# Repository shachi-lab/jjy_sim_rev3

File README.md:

# 📡 JJY Simulator Rev.3 for ESP32-C3 / ESP8684

Build your own JJY time-signal simulator with an ESP32-C3 or ESP8684!  
This compact simulator reproduces the 40 kHz / 60 kHz JJY radio time signal using PWM output,  
based on accurate time obtained from NTP.  
Rev.3 is developed with ESP-IDF.  

Latest version: **R3-1.0.6**

👉 [README 日本語版はこちら](README_ja.md)

---

## 🪛 Features

* Supports both **ESP32-C3** and **ESP8684**
* Full-featured implementation based on **ESP-IDF**
* **Easy AP mode** for Wi-Fi setup with a single button
* **OLED display** for checking the current time and sync status
* Automatic time synchronization via **NTP**
* Switchable **JJY 40 kHz (eastern Japan) / 60 kHz (western Japan)**
* Output **band optimization** can be selected with an on-board switch
* Signal is radiated from a built-in **simple antenna** on the board
* **H-bridge output stage** for higher output power (may transmit farther than expected)
* Configuration page accessible from a **web browser**
* Supports **time zones** and **DST (Daylight Saving Time)**
* **Hourly Mode** for periodic JJY signal output
* **Night Mode** for reducing OLED display brightness at night
* **Offset Time** adjustment for fine-tuning the transmitted time
* Displays a **clock screen** during operation

<br/>

---

## 🛠 Build and Flash (ESP-IDF / CLI)

JJY-SIM R3 is built and flashed using ESP-IDF.  
R2 was Arduino-based,  
but R3 has moved to ESP-IDF for better timing accuracy and a cleaner overall architecture.

> ### ⚠️ Note
> * This project cannot be built in the Arduino environment
> * This is an ESP-IDF-only project

### ■ Environment

* ESP-IDF v5.x
* Python (with a working `idf.py` environment)

For ESP-IDF setup, please refer to the official documentation.

### ■ Build

Move to the project directory and run:

```bash
idf.py build
```

### ■ Flash

```bash
idf.py flash
```

If you need to specify the serial port:

```bash
idf.py -p COMx flash
```

### ■ Serial Monitor

```bash
idf.py monitor
```

### ■ Full Command

```bash
idf.py -p COMx flash monitor
```

This single command lets you flash the firmware and open the log output at the same time.

### ■ Target Selection

Set the target once during initial setup.
The required target depends on which module you are using.

* When using **ESP32-C3**:

```bash
idf.py set-target esp32c3
```

* When using **ESP8684**:
  Since the ESP8684 is based on **ESP32-C2**,
  select `esp32c2` as the chip target.

```bash
idf.py set-target esp32c2
```

---

## 🛠 Build and Flash (VSCode / GUI)

You can also develop this project using **VSCode + the ESP-IDF Extension**.

### ■ Recommended Extension

* ESP-IDF Extension (Espressif)

By installing the extension in VSCode, you can perform the following from the GUI:

* Build
* Flash
* Serial monitor

### ■ Setup

Set up your environment according to the ESP-IDF Extension instructions.

Once the extension is installed, you can run actions such as:

* `Build`
* `Flash`
* `Monitor`

with a single click.

### ■ Workspace

When opening the project in VSCode,
open **`jjy-sim-r3.code-workspace`** in the source-code folder
to work with the ESP-IDF Extension settings already included.

---

## ⚙️ Usage

### ■ Wi-Fi Setup

* After power-on or reset, press the **CONFIG** switch within 5 seconds  
  On first boot, the device enters Wi-Fi setup mode automatically
* An AP named `JJY-SIM-R3-XXXXXXXX` will start
* Connect from a smartphone or PC → a captive portal will appear
* Select the SSID and enter the password
* You can also configure the band, local time, and DST (Daylight Saving Time) as needed
* Click **[Save and Reboot]** to save the settings and restart the device

### ■ Operation Check

* After power-on or reset, the logo is shown. If left untouched for 5 seconds, the device will try to connect to the configured Wi-Fi AP
* Once connected, it obtains the current time from an NTP server
* The current time is shown on the OLED, and JJY signal output starts from second 0 using PWM
* Just press the **receive button** on your radio-controlled clock and place it nearby

### ■ Controls During Operation

While the clock screen is displayed, the following operations are available:

* Press the **[CONFIG]** button for about 1 second to show the information screen  
  Press **[CONFIG]** again to return to the clock screen
* Press and hold the **[CONFIG]** button for 5 seconds or longer to stop JJY transmission output  
  Press and hold **[CONFIG]** again for 5 seconds or longer to resume JJY transmission output

---

## 🔌 Pin Assignment (Main Signals)

| Function       | GPIO | Notes                                                        |
| -------------- | ---- | ------------------------------------------------------------ |
| JJY PWM output | 10,4 | Modulated output signals, inverted A/B pair for the H-bridge |
| CONFIG switch  | 9    | Used for Wi-Fi setup (**shared with BOOT pin**)              |
| ACT LED        | 5    | Activity LED                                                 |
| IND LED        | 0    | Status indicator LED (can be shared)                         |
| OLED Reset     | 2    | OLED module reset                                            |
| OLED SDA       | 7    | OLED I2C data                                                |
| OLED SCL       | 6    | OLED I2C clock                                               |

---

## 🧾 File Structure

### 💻 Firmware

* The firmware source code is located in the **`firmware/idf`** folder.
* This firmware uses a rebuilt library, ported as an IDF component, based on the Arduino OLED driver library used in R2.  
This component is publicly available on GitHub.  
👉 [SSD1306 OLED display driver](https://github.com/Shachi-lab/oled_display)
* `storage_key.h` contains placeholder values and can be used as-is.  
  For better security, you may want to replace them with your own values before building.

### 🧰 Hardware

* The hardware design files are located in the **`hardware`** folder.
* The schematic and PCB design data are in **`hardware/KiCad`**.

  * Compatible with **KiCad Ver.9** only (cannot be opened with Ver.8 or earlier)
  * **Gerber data** is included in **`KiCad/PLOT`**, so the board can be fabricated as-is
* The 3D case data is in **`hardware/case_3d`**.

---

## 📸 Appearance / Assembly Examples

These are the board and case exterior views.  
The design uses a black PCB and a black case so that only the display appears to float visually.

<br/>

---

## ⚠️ Caution

This device may radiate farther than expected.  
Please make sure to comply with applicable radio regulations when experimenting with it.

---

## 🔗 Support / Documentation  

For the latest information, setup guide, and detailed usage notes, please see the support page.  
👉 [JJY-SIM Support Page](https://blog.shachi-lab.com/support/)  
>Note: The support page is currently available in Japanese only.

---
## 📝 Attribution

JJY-SIM is released under the MIT License.  
You are free to use, modify, and build upon this project.  

When selling, distributing, or publicly releasing something based on JJY-SIM, please include attribution to **Shachi-lab / JJY-SIM** somewhere visible, such as the product page, documentation, README, package, or other accompanying materials.

Example:

* Designed by Shachi-lab
* Based on JJY-SIM by Shachi-lab
* Inspired by JJY-SIM by Shachi-lab

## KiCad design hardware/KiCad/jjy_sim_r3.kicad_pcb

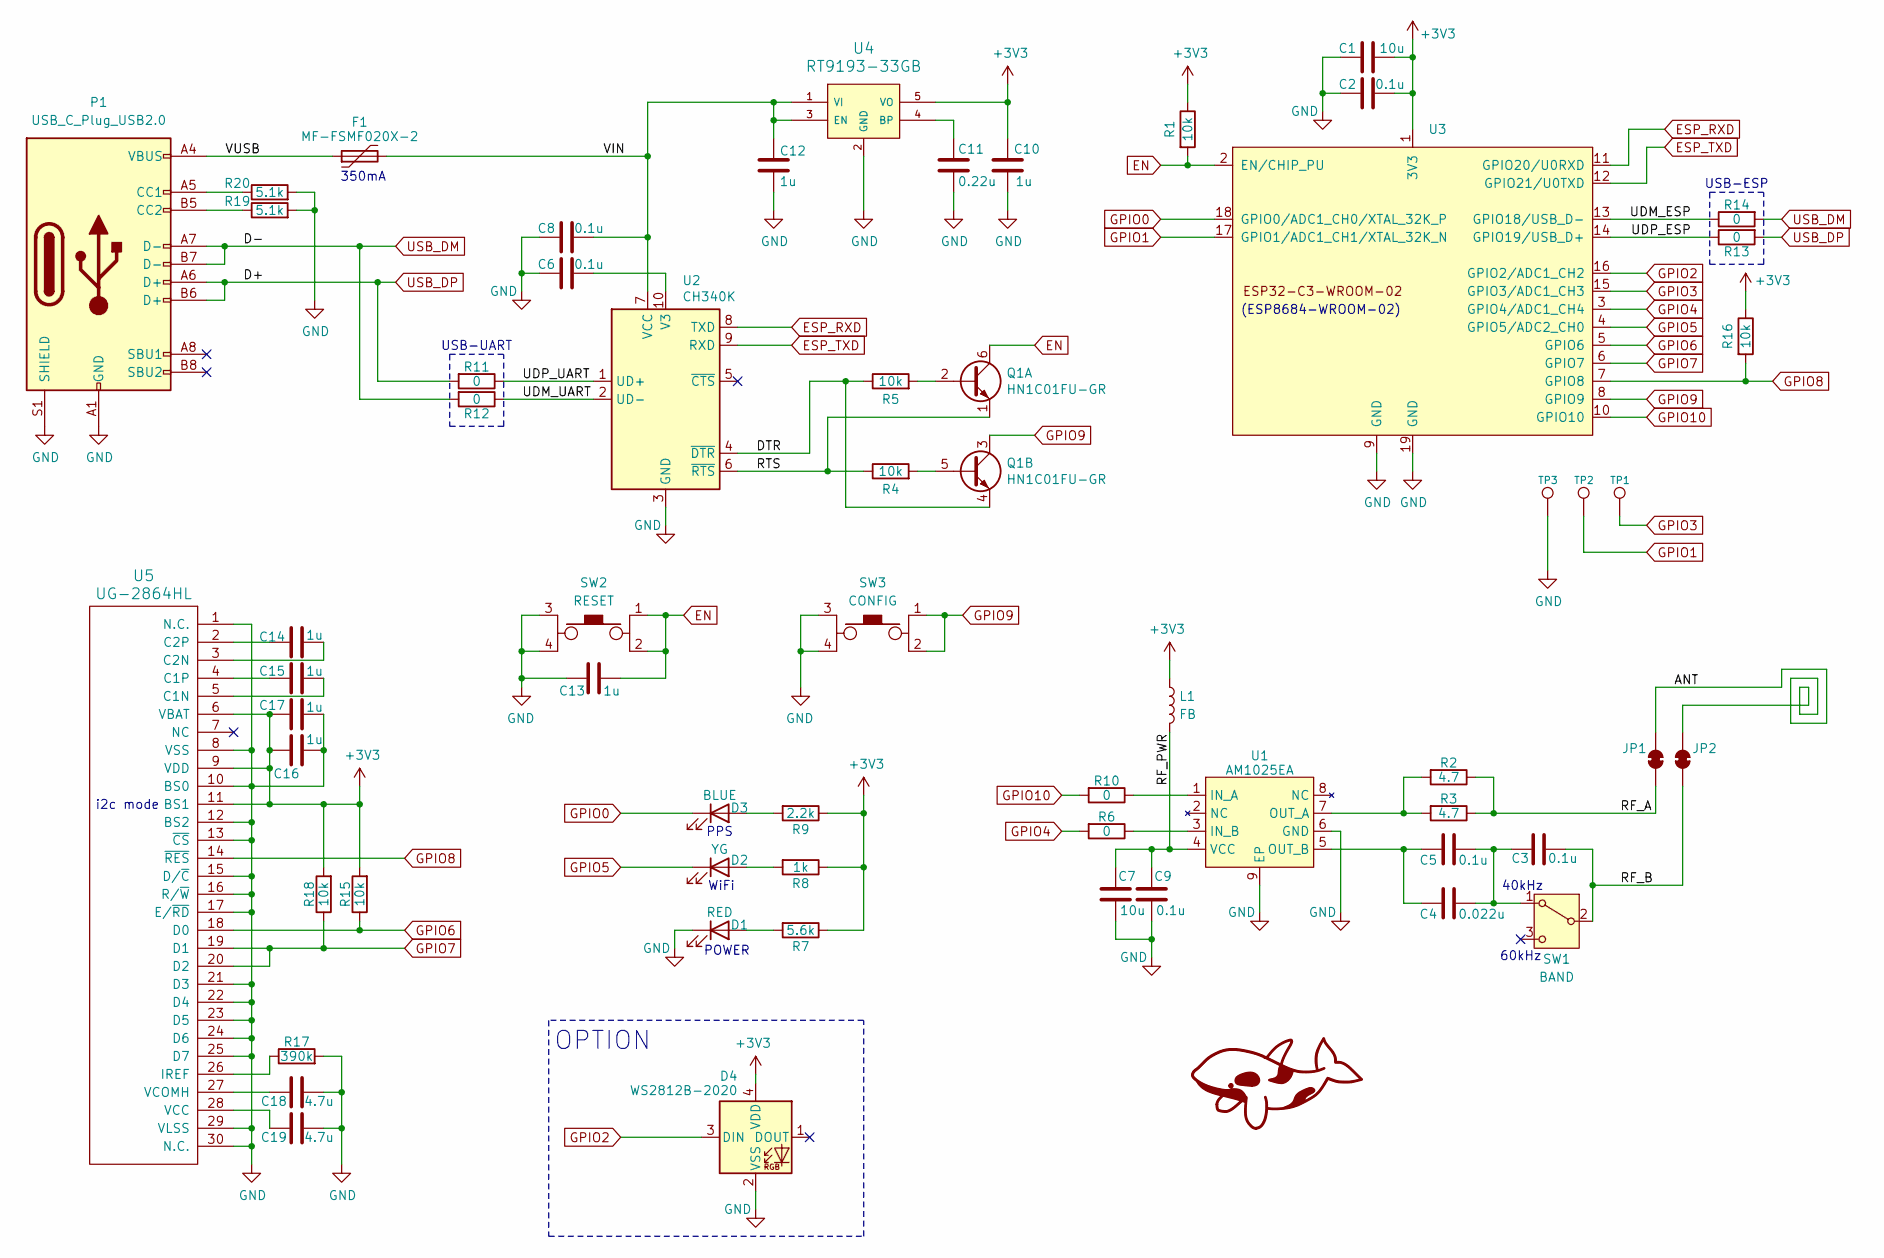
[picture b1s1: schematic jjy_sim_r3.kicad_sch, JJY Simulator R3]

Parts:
C1, C7: 10u; C_0805_2012Metric
C2, C3, C5, C6, C8, C9: 0.1u; C_0603_1608Metric
C4: 0.022u; C_0603_1608Metric
C10, C12, C13, C14, C15, C16, C17: 1u; C_0603_1608Metric
C11: 0.22u; C_0603_1608Metric
C18, C19: 4.7u; C_0603_1608Metric
D1: RED; LED_0603_1608Metric
D2: YG; LED_0603_1608Metric
D3: BLUE; LED_0603_1608Metric
D4: WS2812B-2020; LED_WS2812B-2020_PLCC4_2.0x2.0mm
F1: MF-FSMF020X-2; Fuse_1206_3216Metric_Pad1.42x1.75mm_HandSolder
JP1: ANT-A; Jumper-2_TH_3.81mm
JP2: GND; Jumper-2_TH_3.81mm
L1: FB; L_0603_1608Metric
P1: USB_C_Plug_USB2.0; 5077CR-16SMC2-BK-TR_Ext
Q1: HN1C01FU-GR; 2-2J1A
R1, R4, R5, R15, R16, R18: 10k; R_0603_1608Metric
R2, R3: 4.7; R_0603_1608Metric
R6, R10, R11, R12, R13, R14: 0; R_0603_1608Metric
R7: 5.6k; R_0603_1608Metric
R8: 1k; R_0603_1608Metric
R9: 2.2k; R_0603_1608Metric
R17: 390k; R_0603_1608Metric
R19, R20: 5.1k; R_0603_1608Metric
SW1: BAND; MSK-12C02
SW2: RESET; SKRPACE010
SW3: CONFIG; SKRPACE010
TP1, TP2, TP3: TP; TestPoint_THTPad_D1.5mm_Drill0.7mm
U1: AM1025EA; eSOP-8_3.9x5.05mm_EP_3.1x2.2mm_P1.27mm
U2: CH340K; SSOP-10-1EP_3.9x4.9mm_P1mm_EP2.1x3.3mm
U3: ESP32-C3-WROOM-02; ESP32-C3-WROOM-02,ESP8684-WROOM-2C
U4: RT9193-33GB; SOT-23-5
U5: UG-2864HL; UG-2864-FPC (Reverse)

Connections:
+3V3: C1.2, C2.2, C10.1, C16.1, C17.1, D4.4 (VDD), L1.1, R1.1, R7.1, R8.1, R9.1, R15.2, R16.1, R18.2, U3.1 (3V3), U4.5 (VO), U5.6 (VBAT), U5.9 (VDD), U5.11 (BS1)
/ANT: JP1.2 (B), JP2.2 (B)
/DTR: Q1.4 (E2), R5.1, U2.4 (~DTR)
/RF_A: JP1.1 (A), R2.1, R3.1
/RF_B: C3.2, JP2.1 (A), SW1.2 (B)
/RF_PWR: C7.1, C9.1, L1.2, U1.4 (VCC)
/RTS: Q1.1 (E1), R4.1, U2.6 (~RTS)
/UDM_ESP: R14.1, U3.13 (GPIO18/USB_D-)
/UDM_UART: R12.1, U2.2 (UD-)
/UDP_ESP: R13.1, U3.14 (GPIO19/USB_D+)
/UDP_UART: R11.1, U2.1 (UD+)
/VIN: C8.2, C12.1, F1.2, U2.7 (VCC), U4.1 (VI), U4.3 (EN)
/VUSB: F1.1, P1.A4 (VBUS), P1.A9 (VBUS), P1.B4 (VBUS), P1.B9 (VBUS)
EN: C13.2, Q1.6 (C1), R1.2, SW2.1, SW2.2, U3.2 (EN/CHIP_PU)
ESP_RXD: U2.8 (TXD), U3.11 (GPIO20/U0RXD)
ESP_TXD: U2.9 (RXD), U3.12 (GPIO21/U0TXD)
GND: C1.1, C2.1, C6.1, C7.2, C8.1, C9.2, C10.2, C11.2, C12.2, C13.1, C16.2, C17.2, C18.2, C19.2, D1.1 (K), D4.2 (VSS), P1.A1 (GND), P1.A12 (GND), P1.B1 (GND), P1.B12 (GND), P1.S1 (SHIELD), R17.2, R19.2, R20.2, SW2.3, SW2.4, SW3.3, SW3.4, TP3.1 (1_1), U1.6 (GND), U1.9 (EP), U2.3 (GND), U2.11 (GND), U3.9 (GND), U3.19 (GND), U4.2 (GND), U5.1 (NC(GND)), U5.8 (VSS), U5.10 (BS0), U5.12 (BS2), U5.13 (~CS), U5.15 (D/~C), U5.16 (R/~W), U5.17 (E/~RD), U5.21 (D3), U5.22 (D4), U5.23 (D5), U5.24 (D6), U5.25 (D7), U5.29 (VLSS), U5.30 (NC(GND))
GPIO0: D3.1 (K), U3.18 (GPIO0/ADC1_CH0/XTAL_32K_P)
GPIO1: TP2.1 (1_1), U3.17 (GPIO1/ADC1_CH1/XTAL_32K_N)
GPIO2: D4.3 (DIN), U3.16 (GPIO2/ADC1_CH2)
GPIO3: TP1.1 (1_1), U3.15 (GPIO3/ADC1_CH3)
GPIO4: R6.2, U3.3 (GPIO4/ADC1_CH4)
GPIO5: D2.1 (K), U3.4 (GPIO5/ADC2_CH0)
GPIO6: R15.1, U3.5 (GPIO6), U5.18 (D0)
GPIO7: R18.1, U3.6 (GPIO7), U5.19 (D1), U5.20 (D2)
GPIO8: R16.2, U3.7 (GPIO8), U5.14 (~RES)
GPIO9: Q1.3 (C2), SW3.1, SW3.2, U3.8 (GPIO9)
GPIO10: R10.2, U3.10 (GPIO10)
unnamed: D1.2 (A), R7.2
unnamed: D2.2 (A), R8.2
unnamed: D3.2 (A), R9.2
unnamed: P1.A5 (CC1), R20.1
unnamed: P1.B5 (CC2), R19.1
unnamed: Q1.2 (B1), R5.2
unnamed: Q1.5 (B2), R4.2
unnamed: C3.1, C4.2, C5.2, SW1.1 (A)
unnamed: R10.1, U1.1 (IN_A)
unnamed: R6.1, U1.3 (IN_B)
unnamed: R2.2, R3.2, U1.7 (OUT_A)
unnamed: C4.1, C5.1, U1.5 (OUT_B)
unnamed: C11.1, U4.4 (BP)
unnamed: C15.2, U5.5 (C1N)
unnamed: C15.1, U5.4 (C1P)
unnamed: C14.2, U5.3 (C2N)
unnamed: C14.1, U5.2 (C2P)
unnamed: R17.1, U5.26 (IREF)
unnamed: C19.1, U5.28 (VCC)
unnamed: C18.1, U5.27 (VCOMH)
unnamed: C6.2, U2.10 (V3)
USB_DM: P1.A7 (D-), P1.B7 (D-), R12.2, R14.2
USB_DP: P1.A6 (D+), P1.B6 (D+), R11.2, R13.2

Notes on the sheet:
USB-UART
PPS
OPTION
350mA
i2c mode
60kHz
USB-ESP
WiFi
40kHz
POWER
(ESP8684-WROOM-02)

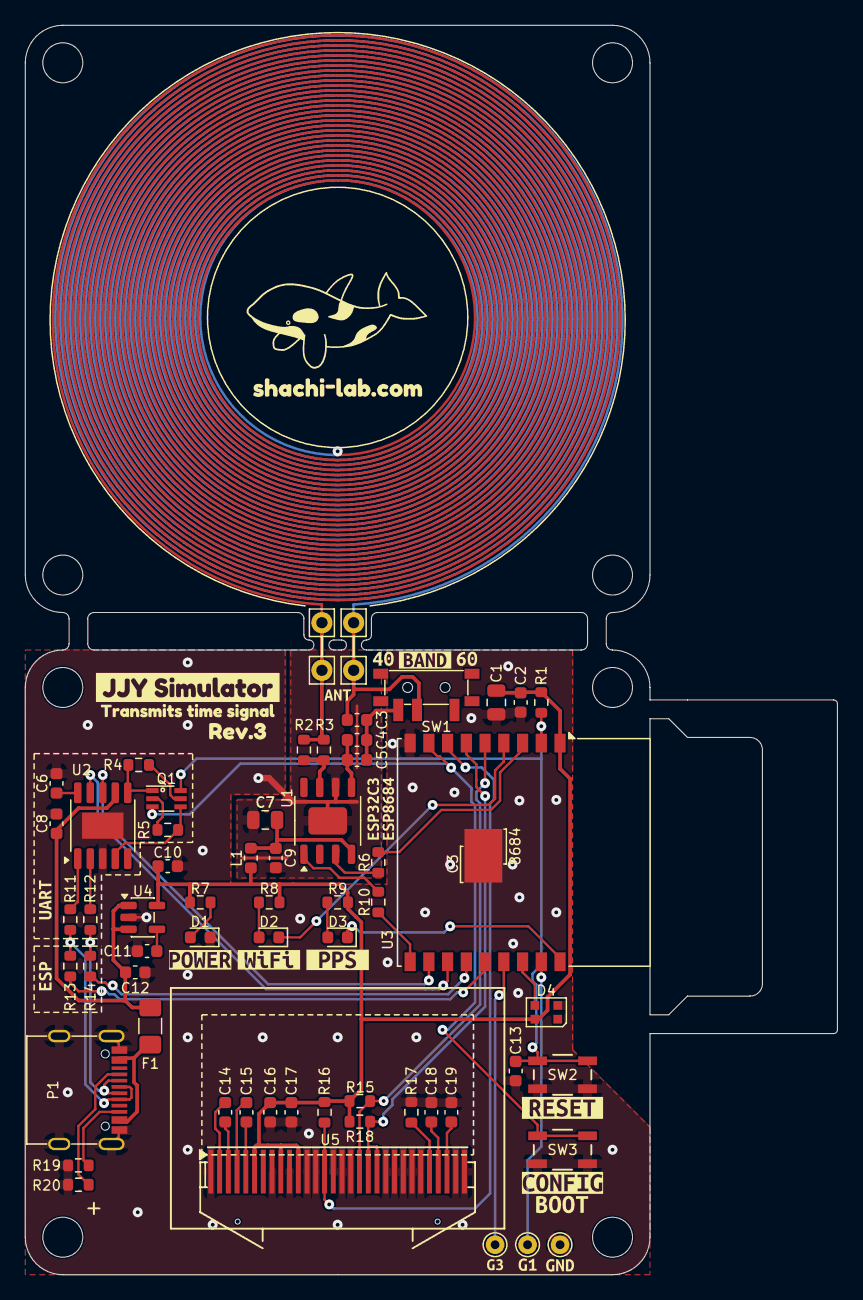
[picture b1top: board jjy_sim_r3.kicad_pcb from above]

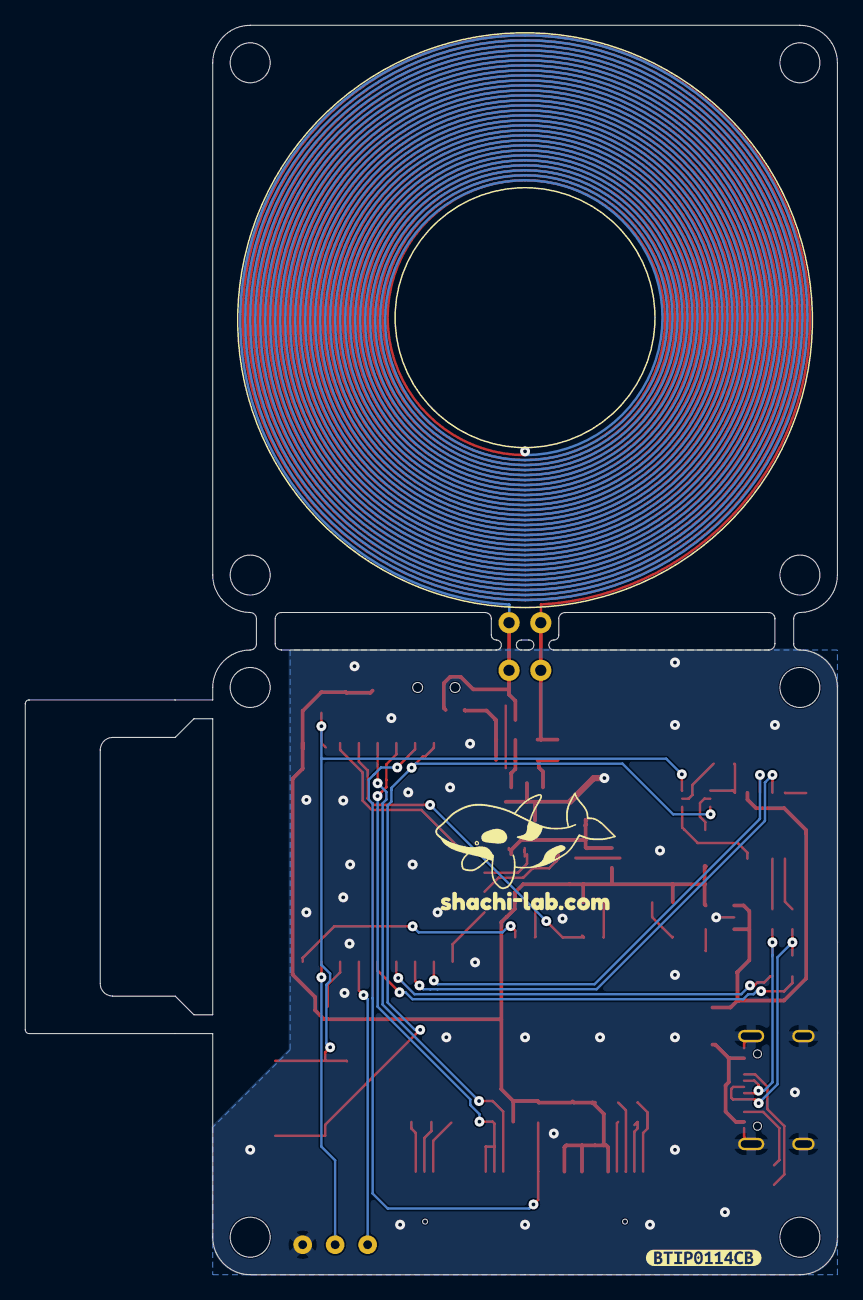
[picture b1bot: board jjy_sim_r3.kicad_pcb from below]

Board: 2 copper layers, 65.0 x 100.0 mm, 90 parts (2 on the bottom side), 51 nets.

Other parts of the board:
1, 2, 3, 4, 5, 6, 7, 8: (no value)
kibuzzard-1, kibuzzard-28: G***; kibuzzard-68D2B4BB
kibuzzard-2: G***; kibuzzard-6982098F
kibuzzard-3: G***; kibuzzard-69820977
kibuzzard-4: G***; kibuzzard-69820ADF
kibuzzard-5: G***; kibuzzard-68D3A9C1
kibuzzard-6: G***; kibuzzard-6646C6AC
kibuzzard-6A179A92: G***; kibuzzard-6A179A92
kibuzzard-7: G***; kibuzzard-68D3A910
kibuzzard-8: G***; kibuzzard-69816480
kibuzzard-9: G***; kibuzzard-69867CAB
kibuzzard-10: G***; kibuzzard-698209E3
kibuzzard-11: G***; kibuzzard-669B6BC9
kibuzzard-12: G***; kibuzzard-669B6DC4
kibuzzard-13: G***; kibuzzard-68E061D7
kibuzzard-14: G***; kibuzzard-69965DBC
kibuzzard-15: G***; kibuzzard-665B3587
kibuzzard-16: G***; kibuzzard-665B357F
kibuzzard-17: G***; kibuzzard-669B16B9
kibuzzard-18: G***; kibuzzard-665A8DD6
kibuzzard-19: G***; kibuzzard-669B4532
kibuzzard-20: G***; kibuzzard-665B35AE

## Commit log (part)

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2026-04-14 1st commit
    First public release
2026-04-19 bug fix
    Increased the HTTP buffer.
2026-04-24 Added brightness setting function
2026-04-25 Add Night mode Add Hourly mode Bug fix Refine behavior
2026-05-28 Update project for KiCad 10.0 and add local libraries
    - Updated KiCad project files for KiCad 10.0
    - Moved the BAND-SW position
    - Added project-local KiCad libraries
    - Included custom libraries that were previously not committed
2026-06-10 R3-1.0.5: Add night mode and offset time
    * Add Night Mode
    * Add Offset Time setting
    * Refactor internal code
    * Confirm build with ESP-IDF 5.5.4
